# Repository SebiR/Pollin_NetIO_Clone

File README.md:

# Pollin NetIO Clone
> [!WARNING]  
> The original design is flawed in many ways. If you want to build this design, you should be prepared for some disappointment!
> If you know what you're doing, go ahead. Otherwise you might want to wait for the improved version.

This is a clone of the original Pollin NetIO board.

## Versions
### Original

* As identical as possible to the original
* outline and placement of the components as close as possible
* Assembly plan of the original works

### Improved (tbd)
* Mechanical identical
* Added capacitors and diodes for stability
* placement of the components as close to the original as possible

Things to improve:
* ATmega32 to 3V3? -> Consider compability of extensions
* More capacitors for the ENC28J60
* Diode + capacitors for the LM317
* Connect RS232 handshake lines -> Arduino bootloader compatible

## Software
The original Pollin Netserver 1.03 (provided on a CD) is in /Software/Netserver.zip

It works just fine with Windows 11.

## Firmware
The original firmware is included.

The MAC address is stored in the EEPROM and can be modified in the .eep file:

So this is MAC address 00:22:F9:01:C4:F4

## Resources
EEPROM Structure: https://www.mikrocontroller.net/topic/112937#1016995

Hardware improvements: https://community.symcon.de/t/p-llins-avr-net-io-langzeitstabilitaet-des-lan-chips/24317/12

General: https://www.mikrocontroller.net/articles/AVR_Net-IO_Bausatz_von_Pollin

## Disclaimer
> [!CAUTION]
> This project was created to archive and preserve the NetIO PCB. Pollin owns all the rights to this design.
> There's no copyright infringement intended, please contact me for removal.

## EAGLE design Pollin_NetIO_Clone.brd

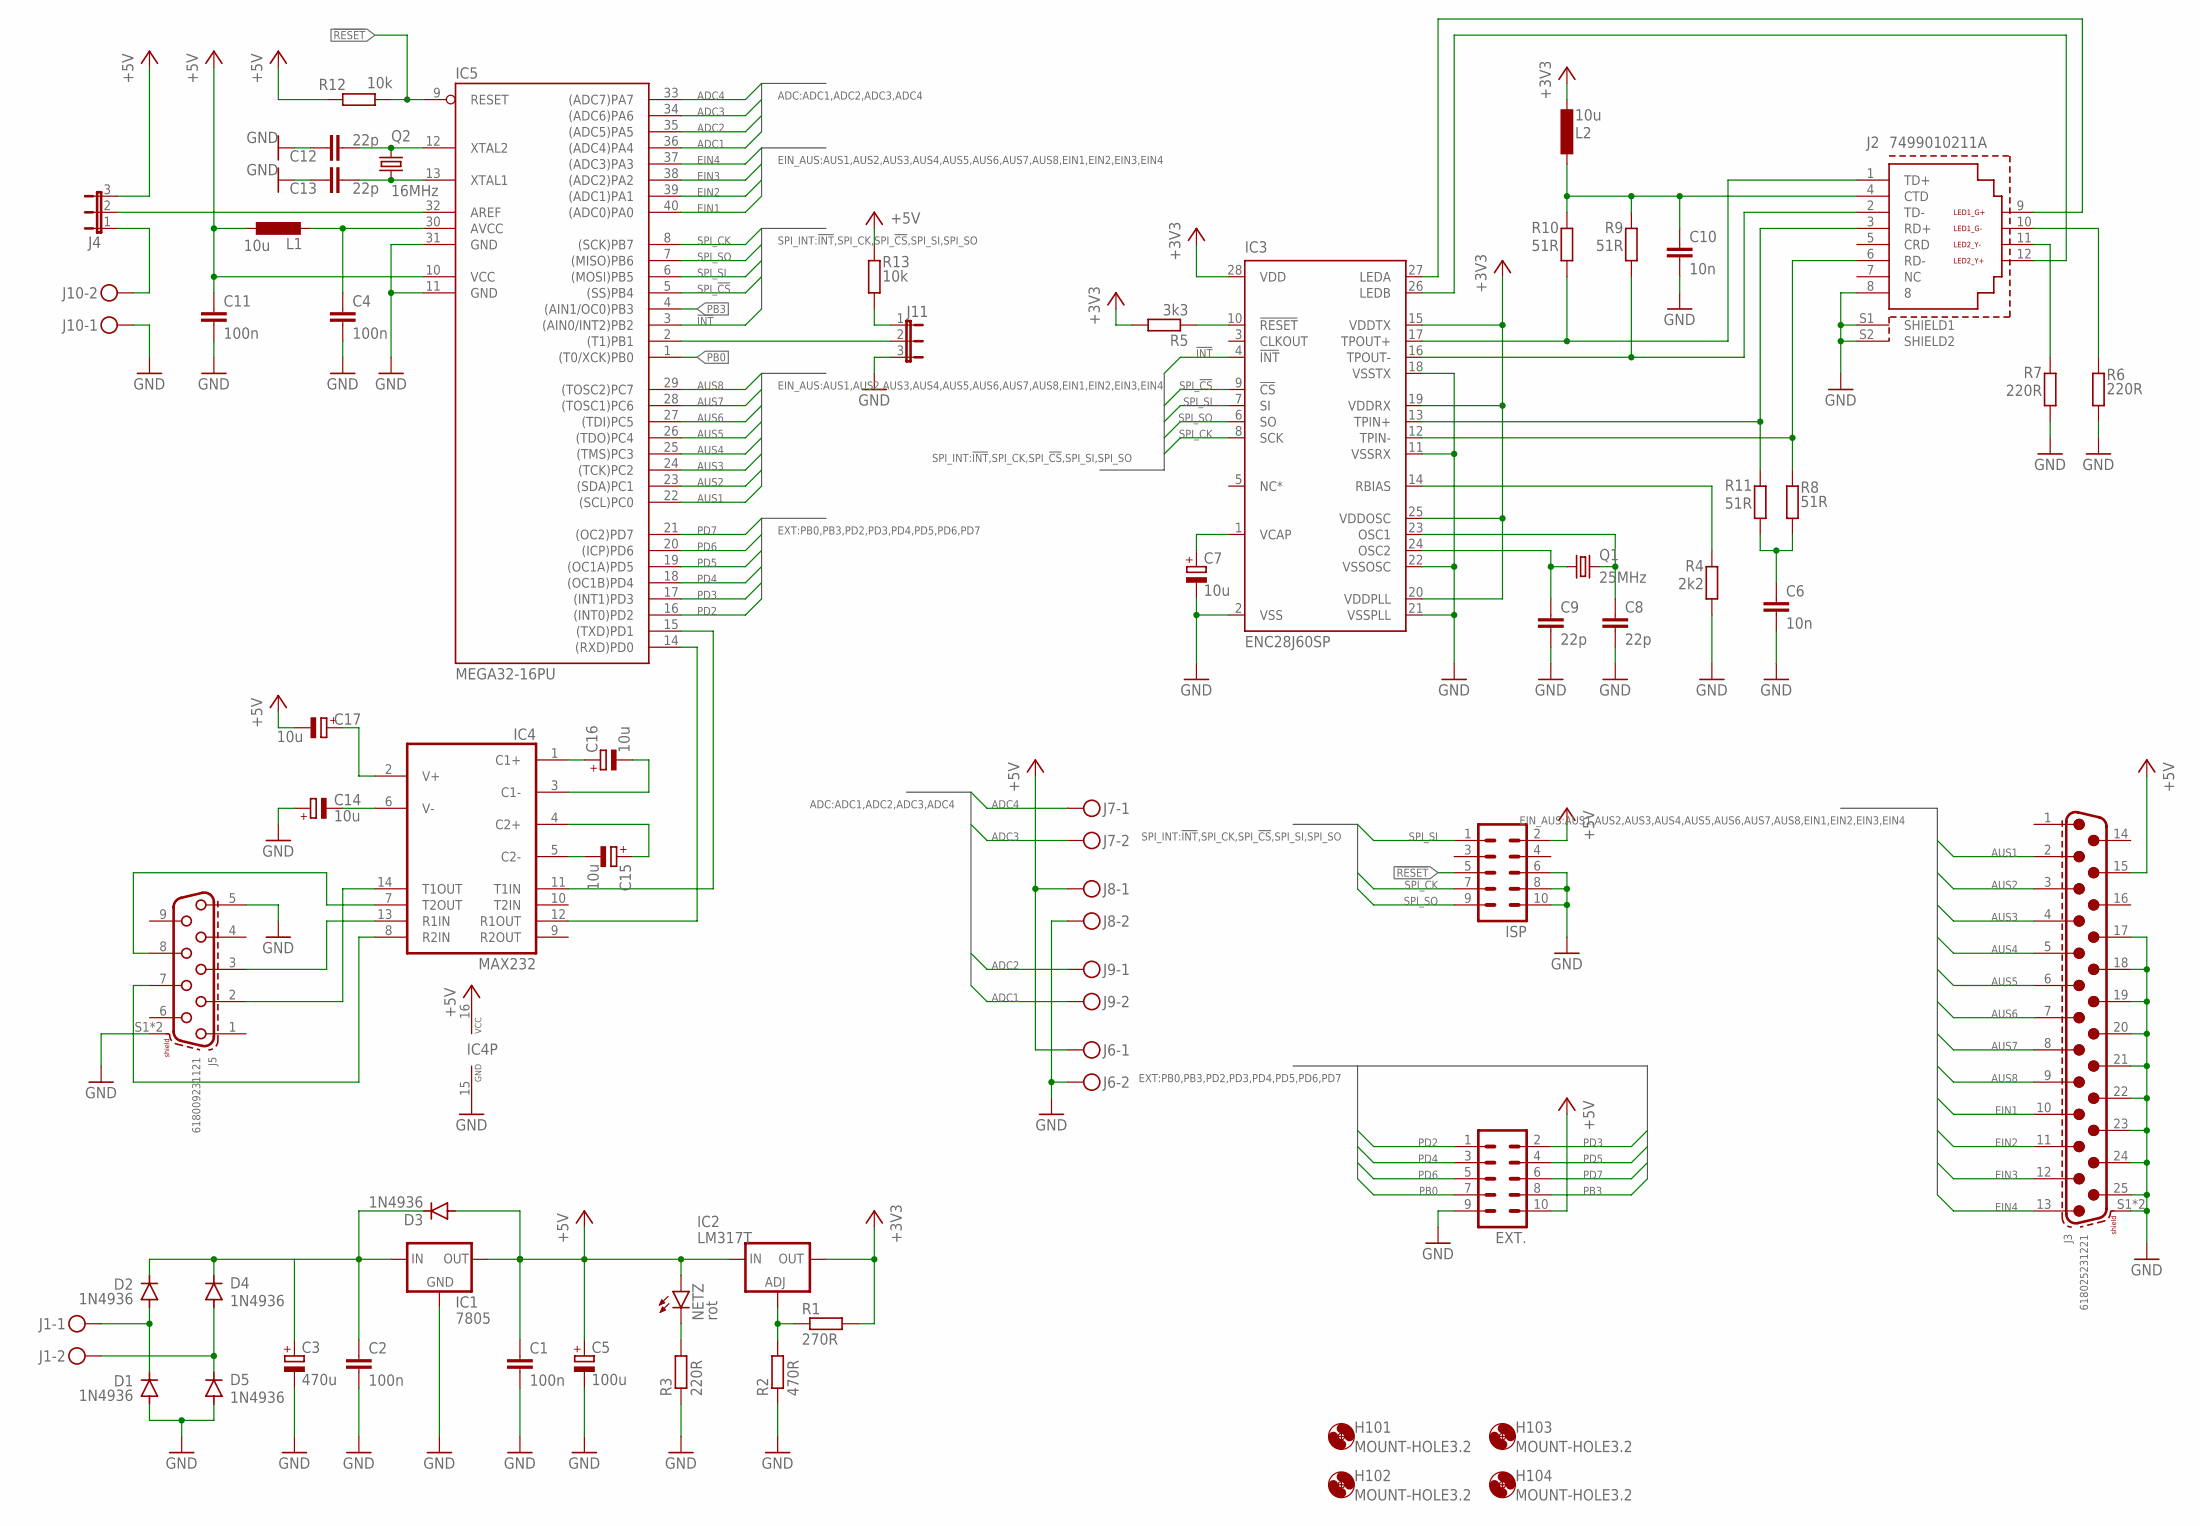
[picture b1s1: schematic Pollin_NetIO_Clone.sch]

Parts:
C1, C2, C4, C11: 100n; C050-025X075
C3: 470u; E5-10,5
C5: 100u; E5-5
C6, C10: 10n; C050-025X075
C7, C14, C15, C16, C17: 10u; E5-5
C8, C9, C12, C13: 22p; C050-024X044
D1, D2, D3, D4, D5: 1N4936; DO41-10
EXT.: ML10
H101, H102, H103, H104: MOUNT-HOLE3.2; 3,2
IC1: 7805; 78XXS
IC2: LM317T; 317TS
IC3: ENC28J60SP; DIL28-3
IC4: MAX232; DIL16
IC5: MEGA32-16PU; DIL40
ISP: ML10
J1, J6, J7, J8, J9, J10: MKDSN1,5/2-5,08
J2: 7499010211A
J3: 618025231221
J4, J11: JP2E; JP2
J5: 618009231121
L1, L2: 10u; 0207/15
NETZ: rot; LED5MM
Q1: 25MHz; HC49/S
Q2: 16MHz; HC49/S
R1: 270R; 0207/10
R2: 470R; 0207/10
R3, R6, R7: 220R; 0207/10
R4: 2k2; 0207/10
R5: 3k3; 0207/10
R8, R9, R10, R11: 51R; 0207/10
R12, R13: 10k; 0207/10

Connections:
!INT: IC3.4 (!INT), IC5.3 ((AIN0/INT2)PB2)
!RESET: IC5.9 (RESET), ISP.5, R12.2
+3V3: IC2.2 (OUT), IC3.15 (VDDTX), IC3.19 (VDDRX), IC3.20 (VDDPLL), IC3.25 (VDDOSC), IC3.28 (VDD), L2.2, R1.2, R5.2
+5V: C1.1, C5.+, C11.1, C17.-, D3.A, EXT..10, IC1.OUT, IC2.3 (IN), IC4.16 (VCC), IC5.10 (VCC), ISP.2, J3.15, J4.3, J6.1, J8.1, L1.1, NETZ.A, R12.1, R13.2
ADC1: IC5.36 ((ADC4)PA4), J9.2
ADC2: IC5.35 ((ADC5)PA5), J9.1
ADC3: IC5.34 ((ADC6)PA6), J7.2
ADC4: IC5.33 ((ADC7)PA7), J7.1
AREF: IC5.32 (AREF), J4.2
AREF_EXT: J4.1, J10.2
AUS1: IC5.22 ((SCL)PC0), J3.2
AUS2: IC5.23 ((SDA)PC1), J3.3
AUS3: IC5.24 ((TCK)PC2), J3.4
AUS4: IC5.25 ((TMS)PC3), J3.5
AUS5: IC5.26 ((TDO)PC4), J3.6
AUS6: IC5.27 ((TDI)PC5), J3.7
AUS7: IC5.28 ((TOSC1)PC6), J3.8
AUS8: IC5.29 ((TOSC2)PC7), J3.9
AVCC: C4.1, IC5.30 (AVCC), L1.2
EIN1: IC5.40 ((ADC0)PA0), J3.10
EIN2: IC5.39 ((ADC1)PA1), J3.11
EIN3: IC5.38 ((ADC2)PA2), J3.12
EIN4: IC5.37 ((ADC3)PA3), J3.13
GND: C1.2, C2.2, C3.-, C4.2, C5.-, C6.2, C7.-, C8.2, C9.2, C10.2, C11.2, C12.1, C13.1, C14.+, D1.A, D5.A, EXT..9, IC1.GND, IC3.2 (VSS), IC3.11 (VSSRX), IC3.18 (VSSTX), IC3.21 (VSSPLL), IC3.22 (VSSOSC), IC4.15 (GND), IC5.11 (GND), IC5.31 (GND), ISP.6, ISP.8, ISP.10, J2.8, J2.S1 (SHIELD1), J2.S2 (SHIELD2), J3.17, J3.18, J3.19, J3.20, J3.21, J3.22, J3.23, J3.24, J3.25, J3.S1 (SHIELD), J3.S2 (SHIELD), J5.5, J5.S1 (SHIELD), J5.S2 (SHIELD), J6.2, J8.2, J10.1, J11.3, R2.1, R3.1, R4.1, R6.1, R7.1
LEDA: IC3.27 (LEDA), J2.9 (LED1_G+)
LEDB: IC3.26 (LEDB), J2.12 (LED2_Y+)
unnamed: C12.2, IC5.12 (XTAL2), Q2.2
unnamed: C13.2, IC5.13 (XTAL1), Q2.1
unnamed: IC5.2 ((T1)PB1), J11.2
unnamed: C8.1, IC3.23 (OSC1), Q1.1
unnamed: C9.1, IC3.24 (OSC2), Q1.2
unnamed: D1.C, D2.A, J1.1
unnamed: D4.A, D5.C, J1.2
unnamed: C2.1, C3.+, D2.C, D3.C, D4.C, IC1.IN
unnamed: NETZ.K (C), R3.2
unnamed: IC3.14 (RBIAS), R4.2
unnamed: IC2.1 (ADJ), R1.1, R2.2
unnamed: IC3.10 (!RESET), R5.1
unnamed: IC3.17 (TPOUT+), J2.1 (TD+), R10.1
unnamed: IC3.16 (TPOUT-), J2.2 (TD-), R9.1
unnamed: IC3.13 (TPIN+), J2.3 (RD+), R11.2
unnamed: IC3.12 (TPIN-), J2.6 (RD-), R8.2
unnamed: C10.1, J2.4 (CTD), L2.1, R9.2, R10.2
unnamed: C6.1, R8.1, R11.1
unnamed: J11.1, R13.1
unnamed: C7.+, IC3.1 (VCAP)
unnamed: C16.+, IC4.1 (C1+)
unnamed: C16.-, IC4.3 (C1-)
unnamed: C15.+, IC4.4 (C2+)
unnamed: C15.-, IC4.5 (C2-)
unnamed: C17.+, IC4.2 (V+)
unnamed: C14.-, IC4.6 (V-)
unnamed: IC4.7 (T2OUT), J5.8
unnamed: IC4.8 (R2IN), J5.7
unnamed: IC4.14 (T1OUT), J5.2
unnamed: IC4.13 (R1IN), J5.3
unnamed: J2.11 (LED2_Y-), R7.2
unnamed: J2.10 (LED1_G-), R6.2
PB0: EXT..7, IC5.1 ((T0/XCK)PB0)
PB3: EXT..8, IC5.4 ((AIN1/OC0)PB3)
PD2: EXT..1, IC5.16 ((INT0)PD2)
PD3: EXT..2, IC5.17 ((INT1)PD3)
PD4: EXT..3, IC5.18 ((OC1B)PD4)
PD5: EXT..4, IC5.19 ((OC1A)PD5)
PD6: EXT..5, IC5.20 ((ICP)PD6)
PD7: EXT..6, IC5.21 ((OC2)PD7)
RXD: IC4.12 (R1OUT), IC5.14 ((RXD)PD0)
SPI_!CS: IC3.9 (!CS), IC5.5 ((SS)PB4)
SPI_CK: IC3.8 (SCK), IC5.8 ((SCK)PB7), ISP.7
SPI_SI: IC3.7 (SI), IC5.6 ((MOSI)PB5), ISP.1
SPI_SO: IC3.6 (SO), IC5.7 ((MISO)PB6), ISP.9
TXD: IC4.11 (T1IN), IC5.15 ((TXD)PD1)

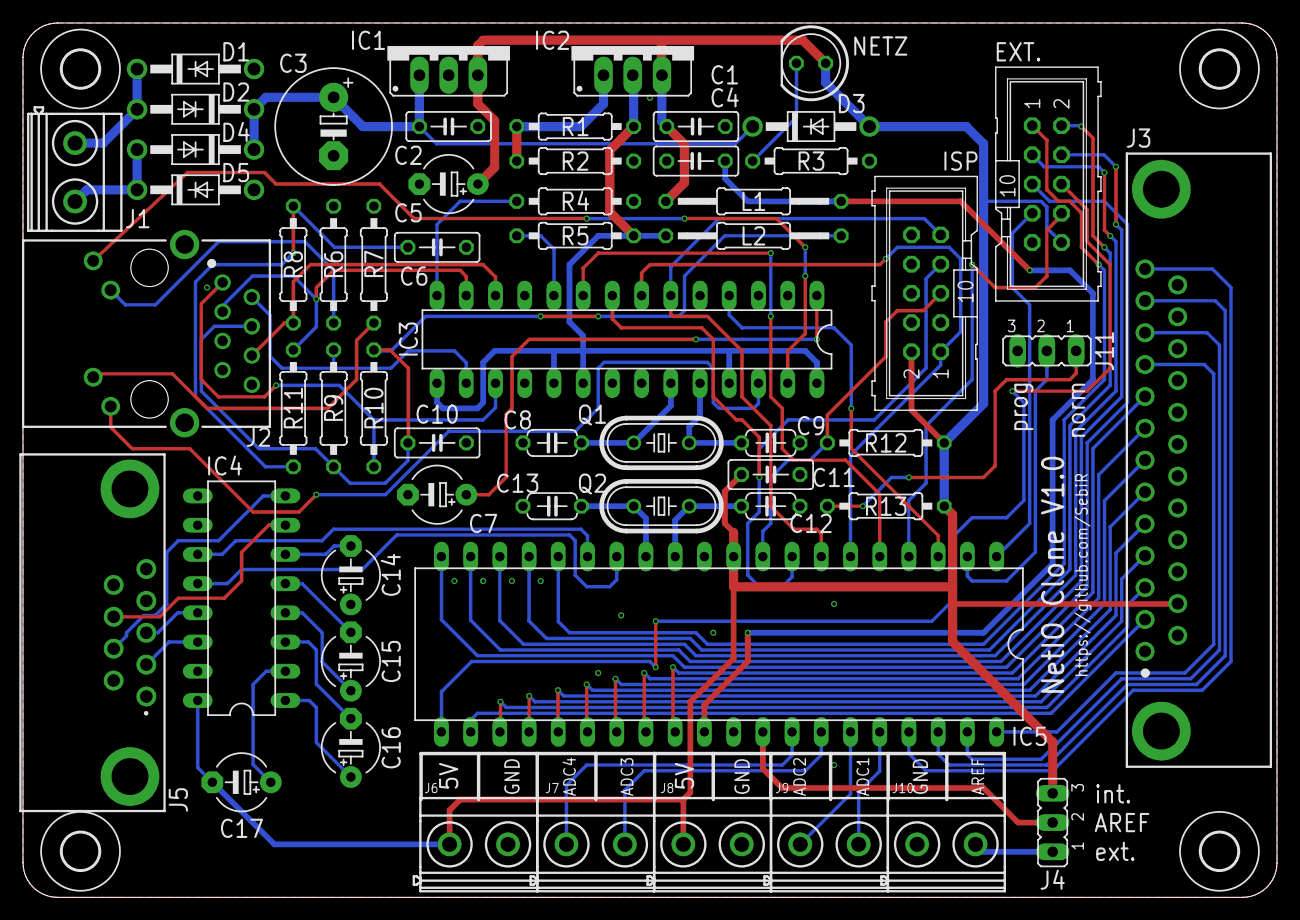
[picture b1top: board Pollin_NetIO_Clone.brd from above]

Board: 2 copper layers, 109.0 x 76.0 mm, 62 parts (0 on the bottom side), 72 nets.

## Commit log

2024-07-13 initial commit of original version
2024-07-13 Added schematic Output/Pollin_NetIO_Clone_SCHEMATIC.pdf
2024-07-13 * cleanded up schematic * changed RJ45 connector to something compatible with the original one
2024-07-14 * Minor Changes in SCH and BRD * Added original Firmware and EEPROM file * Added STEP model
2024-07-14 * Updated schematic pdf * Added gerber files
2024-07-14 * Added contents of original CD
2024-07-14 * Added bootloader.hex from Netserver
2024-07-14 fixed typo in readme
2024-07-15 Added warning
2024-07-15 * Added simple arduino test sketch
2024-07-15 * Fixed fuse settings * Changed eep file to default IP
2024-07-15 changed readme
2024-07-15 added own pictures
2024-07-15 small changes
2024-08-25 Small Updates in the Layout

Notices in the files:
parts and their libraries:
Wurth_Connectors_WR-DSUB: Copyright: Würth Elektronik
